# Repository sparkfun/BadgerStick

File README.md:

Interactive Badges
==================

 [*SparkFun BadgerHack *](https://learn.sparkfun.com/tutorials/badgerhack)
 
 These badges were designed as a soldering demo for the SparkFun booths at Maker Faire. 
 They were designed to teach the basics of PTH soldering, as well as to provide users with an Arduino platform they could take home and hack.
 
Please view the [BadgerHack tutorial](https://learn.sparkfun.com/tutorials/badgerhack) for more information on updating the firmware, and further experiments with your badge. 
 
 Repository Contents
-------------------

* **/badgerstick/avr** - Board definition files for Arduino.
* **/Documentation** - SoftwareSerial Baud Rate table
* **/Firmware** - Default firmware that ships on the BadgerStick
* **/Hardware** - All Eagle design files (.brd, .sch)
* **/Production** - Test bed files and production panel files

Documentation
--------------
* **[Library](https://github.com/sparkfun/SparkFun_LED_Array_8x7_Arduino_Library)** - Arduino library for the BadgerStick.
* **[Hookup Guide](https://learn.sparkfun.com/tutorials/badgerhack)** - Basic hookup guide for the BadgerStick. 
* **[SparkFun Fritzing repo](https://github.com/sparkfun/Fritzing_Parts)** - Fritzing diagrams for SparkFun products.
* **[SparkFun 3D Model repo](https://github.com/sparkfun/3D_Models)** - 3D models of SparkFun products. 
* **[SparkFun Graphical Datasheets](https://github.com/sparkfun/Graphical_Datasheets)** -Graphical Datasheets for various SparkFun products.

License Information
-------------------

This product is _**open source**_! 

Please review the LICENSE.md file for license information. 

If you have any questions or concerns on licensing, please contact techsupport@sparkfun.com.

Distributed as-is; no warranty is given.

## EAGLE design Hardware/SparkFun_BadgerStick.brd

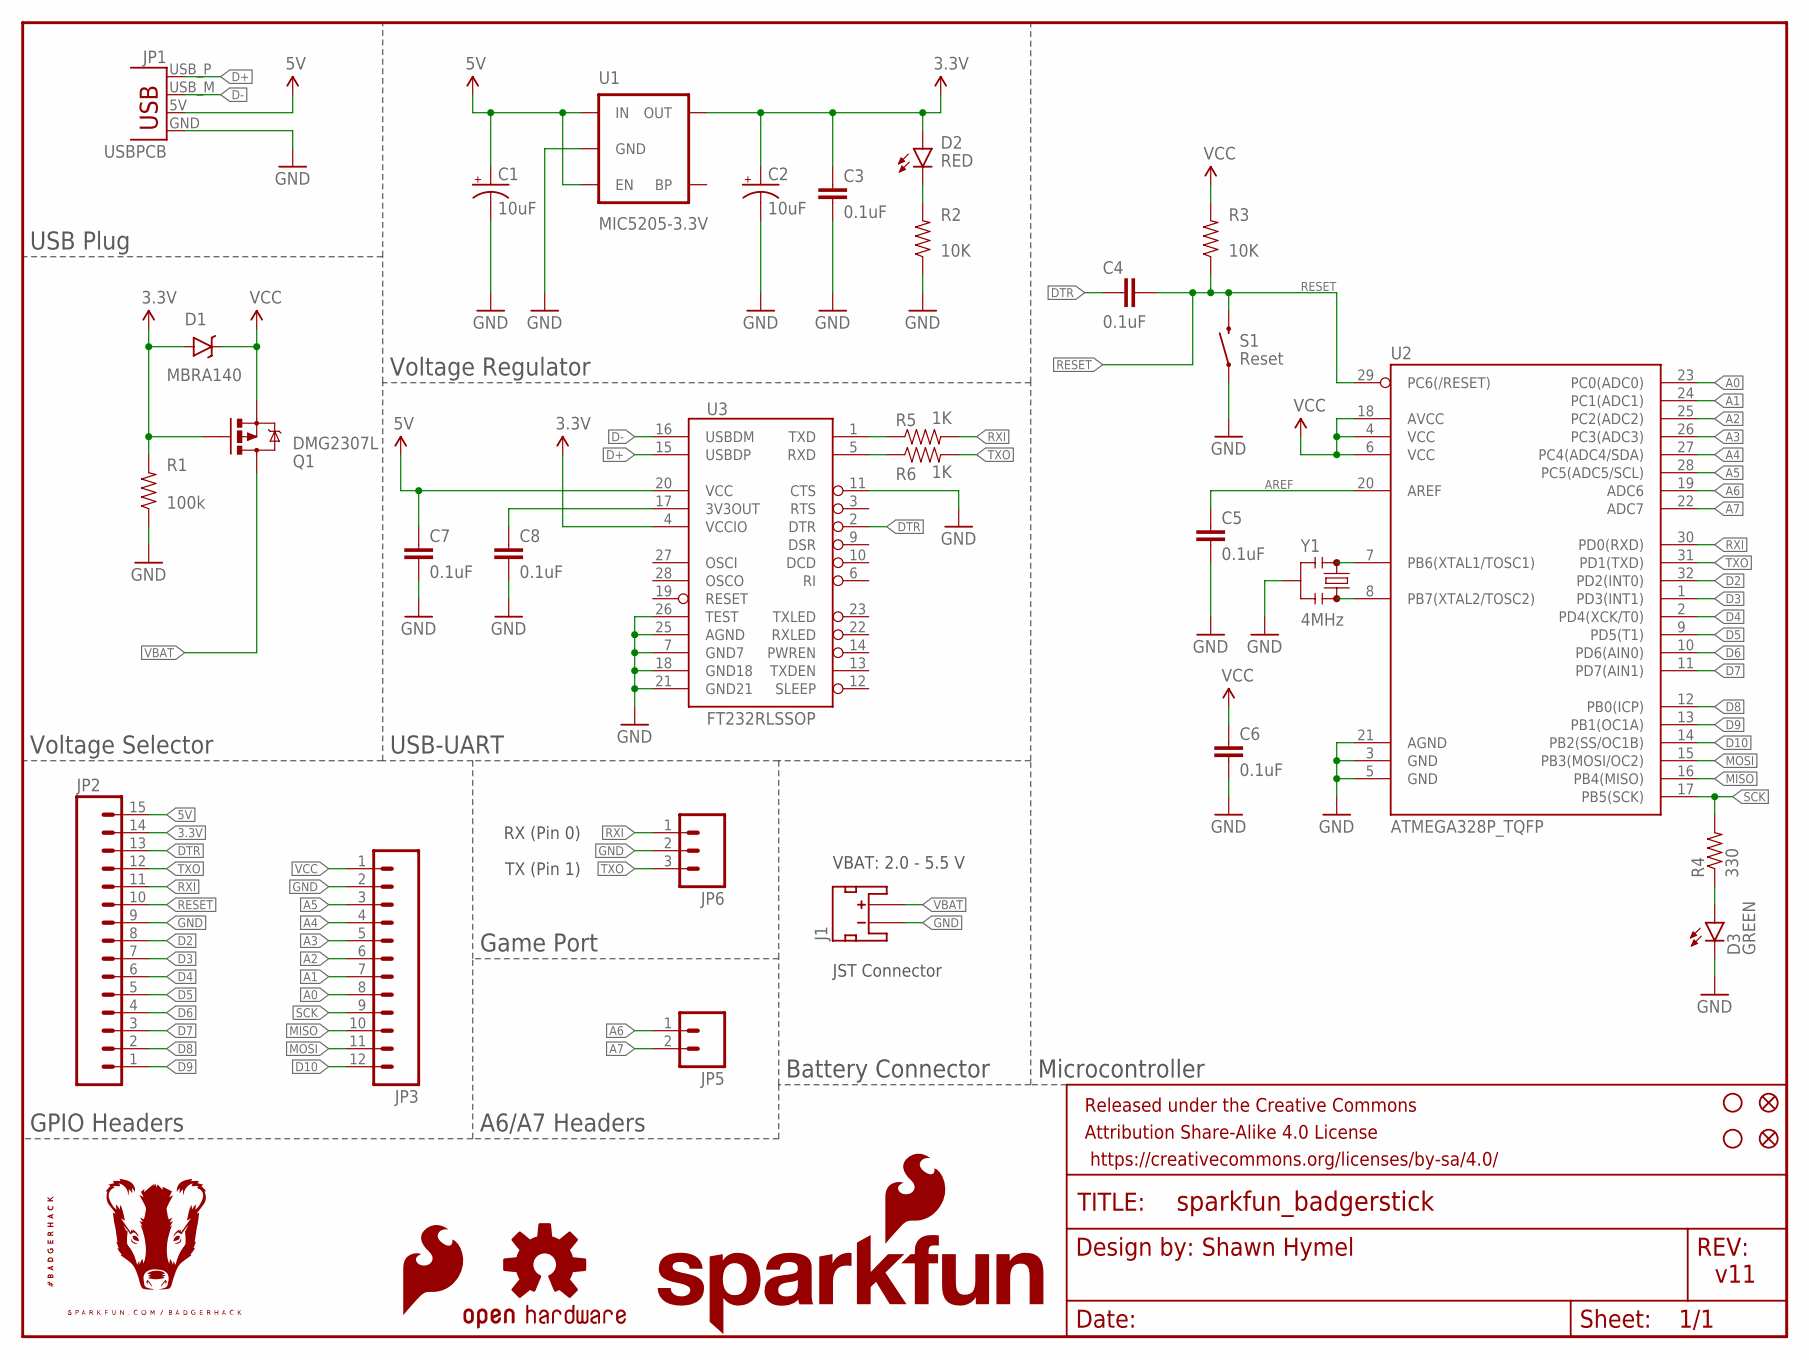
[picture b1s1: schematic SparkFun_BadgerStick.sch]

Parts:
C1, C2: 10uF; EIA3216
C3, C4, C5, C6, C7, C8: 0.1uF; 0603-CAP
D1: MBRA140; SMA-DIODE
D2: RED; LED-0603
D3: GREEN; LED-0603
FID1, FID2: FIDUCIAL1X2; FIDUCIAL-1X2
FRAME1: FRAME-LETTER; CREATIVE_COMMONS
J1: JST_2MM_MALE; JST-2-SMD
JP1: USBPCB; USB-A-PCB
JP2: M15LOCK_NO_SILK; 1X15_LOCK_NO_SILK
JP3: M12LOCK_NO_SILK; 1X12_LOCK_NO_SILK
JP5: M021X02_NO_SILK; 1X02_NO_SILK
JP6: M03LOCK Female; 1X03_LOCK_NO_SILK
LOGO1: SFE_LOGO_FLAME.1_INCH; SFE_LOGO_FLAME_.1
LOGO2: OSHW-LOGOS; OSHW-LOGO-S
Q1: DMG2307L; SOT23-3
R1: 100k; 0603-RES
R2, R3: 10K; 0603-RES
R4: 330; 0603-RES
R5, R6: 1K; 0603-RES
S1: SWITCH-MOMENTARY-2SMD-REDUNDANT; TACTILE-SWITCH-SMD
STANDOFF1, STANDOFF2: STAND-OFF
U1: MIC5205-3.3V; SOT23-5
U2: ATMEGA328P_TQFP; TQFP32-08
U3: FT232RLSSOP; SSOP28DB
U$1: SFE_LOGO_NAME_FLAME.1_INCH; SFE_LOGO_NAME_FLAME_.1
U$2: BADGERHACK_LOGODUMMY; DUMMY
Y1: 4MHz; RESONATOR-SMD_MED

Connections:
3.3V: C2.A (+), C3.1, D1.A, D2.A, JP2.14, Q1.1 (G), R1.2, U1.5 (OUT), U3.4 (VCCIO)
5V: C1.A (+), C7.1, JP1.5V (VBUS), JP2.15, U1.1 (IN), U1.3 (EN), U3.20 (VCC)
A0: JP3.8, U2.23 (PC0(ADC0))
A1: JP3.7, U2.24 (PC1(ADC1))
A2: JP3.6, U2.25 (PC2(ADC2))
A3: JP3.5, U2.26 (PC3(ADC3))
A4: JP3.4, U2.27 (PC4(ADC4/SDA))
A5: JP3.3, U2.28 (PC5(ADC5/SCL))
A6: JP5.1, U2.19 (ADC6)
A7: JP5.2, U2.22 (ADC7)
AREF: C5.1, U2.20 (AREF)
D2: JP2.8, U2.32 (PD2(INT0))
D3: JP2.7, U2.1 (PD3(INT1))
D4: JP2.6, U2.2 (PD4(XCK/T0))
D5: JP2.5, U2.9 (PD5(T1))
D6: JP2.4, U2.10 (PD6(AIN0))
D7: JP2.3, U2.11 (PD7(AIN1))
D8: JP2.2, U2.12 (PB0(ICP))
D9: JP2.1, U2.13 (PB1(OC1A))
D10: JP3.12, U2.14 (PB2(SS/OC1B))
D+: JP1.USB_P (D+), U3.15 (USBDP)
D-: JP1.USB_M (D-), U3.16 (USBDM)
DTR: C4.1, JP2.13, U3.2 (DTR)
GND: C1.C (-), C2.C (-), C3.2, C5.2, C6.2, C7.2, C8.2, D3.C, J1.1 (-), JP1.GND, JP2.9, JP3.2, JP6.2, R1.1, R2.1, S1.1, S1.2 (1), U1.2 (GND), U2.3 (GND), U2.5 (GND), U2.21 (AGND), U3.7 (GND7), U3.11 (CTS), U3.18 (GND18), U3.21 (GND21), U3.25 (AGND), U3.26 (TEST), Y1.2
MISO: JP3.10, U2.16 (PB4(MISO))
MOSI: JP3.11, U2.15 (PB3(MOSI/OC2))
unnamed: D3.A, R4.1
unnamed: C8.1, U3.17 (3V3OUT)
unnamed: R5.1, U3.1 (TXD)
unnamed: D2.C, R2.2
unnamed: U2.7 (PB6(XTAL1/TOSC1)), Y1.1
unnamed: U2.8 (PB7(XTAL2/TOSC2)), Y1.3
unnamed: R6.1, U3.5 (RXD)
RESET: C4.2, JP2.10, R3.1, S1.3 (2), S1.4 (2), U2.29 (PC6(/RESET))
RXI: JP2.11, JP6.1, R5.2, U2.30 (PD0(RXD))
SCK: JP3.9, R4.2, U2.17 (PB5(SCK))
TXO: JP2.12, JP6.3, R6.2, U2.31 (PD1(TXD))
VBAT: J1.2 (+), Q1.3 (D)
VCC: C6.1, D1.C, JP3.1, Q1.2 (S), R3.2, U2.4 (VCC), U2.6 (VCC), U2.18 (AVCC)

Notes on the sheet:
RX (Pin 0)
TX (Pin 1)
USB Plug
Voltage Selector
GPIO Headers
A6/A7 Headers
Game Port
USB-UART
Voltage Regulator
Microcontroller
Battery Connector
VBAT: 2.0 - 5.5 V
JST Connector

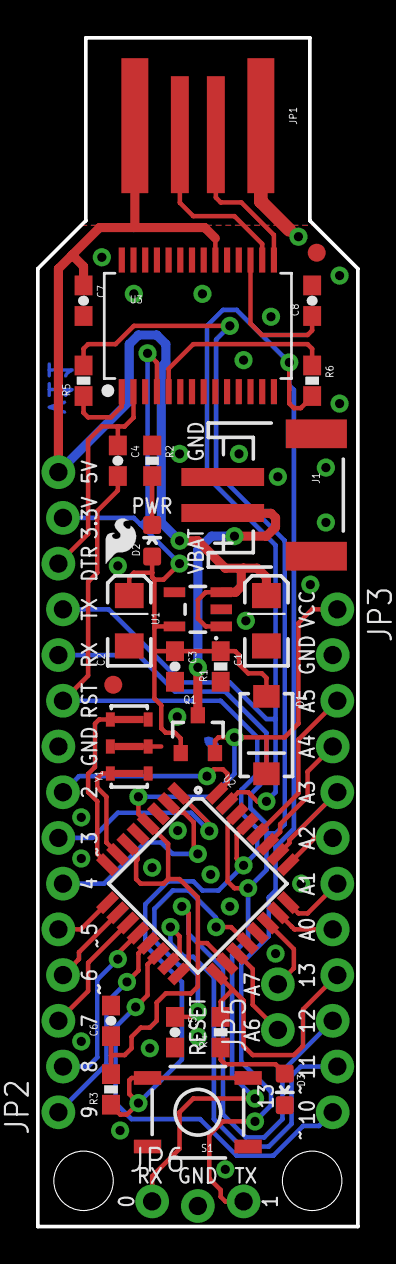
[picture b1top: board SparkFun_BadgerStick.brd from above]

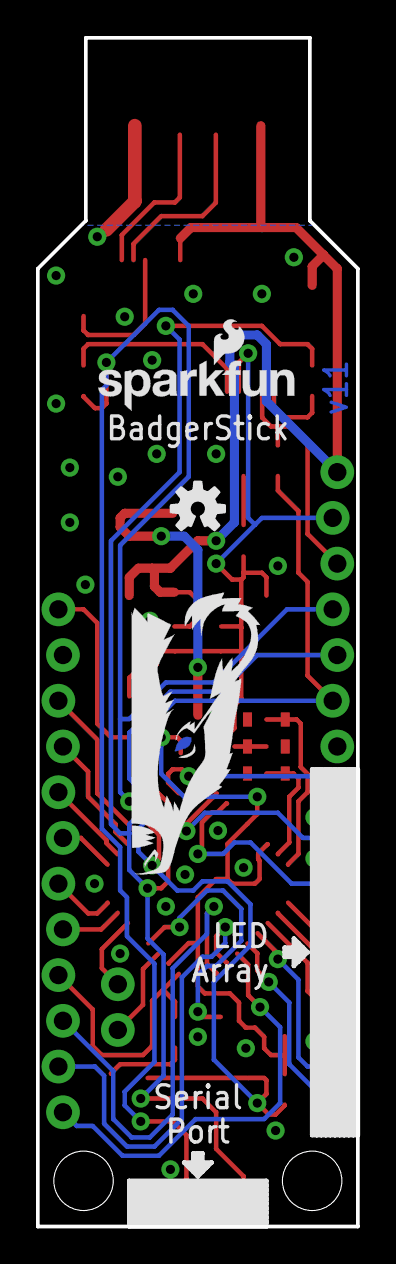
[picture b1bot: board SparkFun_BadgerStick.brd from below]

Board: 2 copper layers, 17.8 x 66.0 mm, 39 parts (3 on the bottom side), 39 nets.

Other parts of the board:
U$3: HALF_BADGER

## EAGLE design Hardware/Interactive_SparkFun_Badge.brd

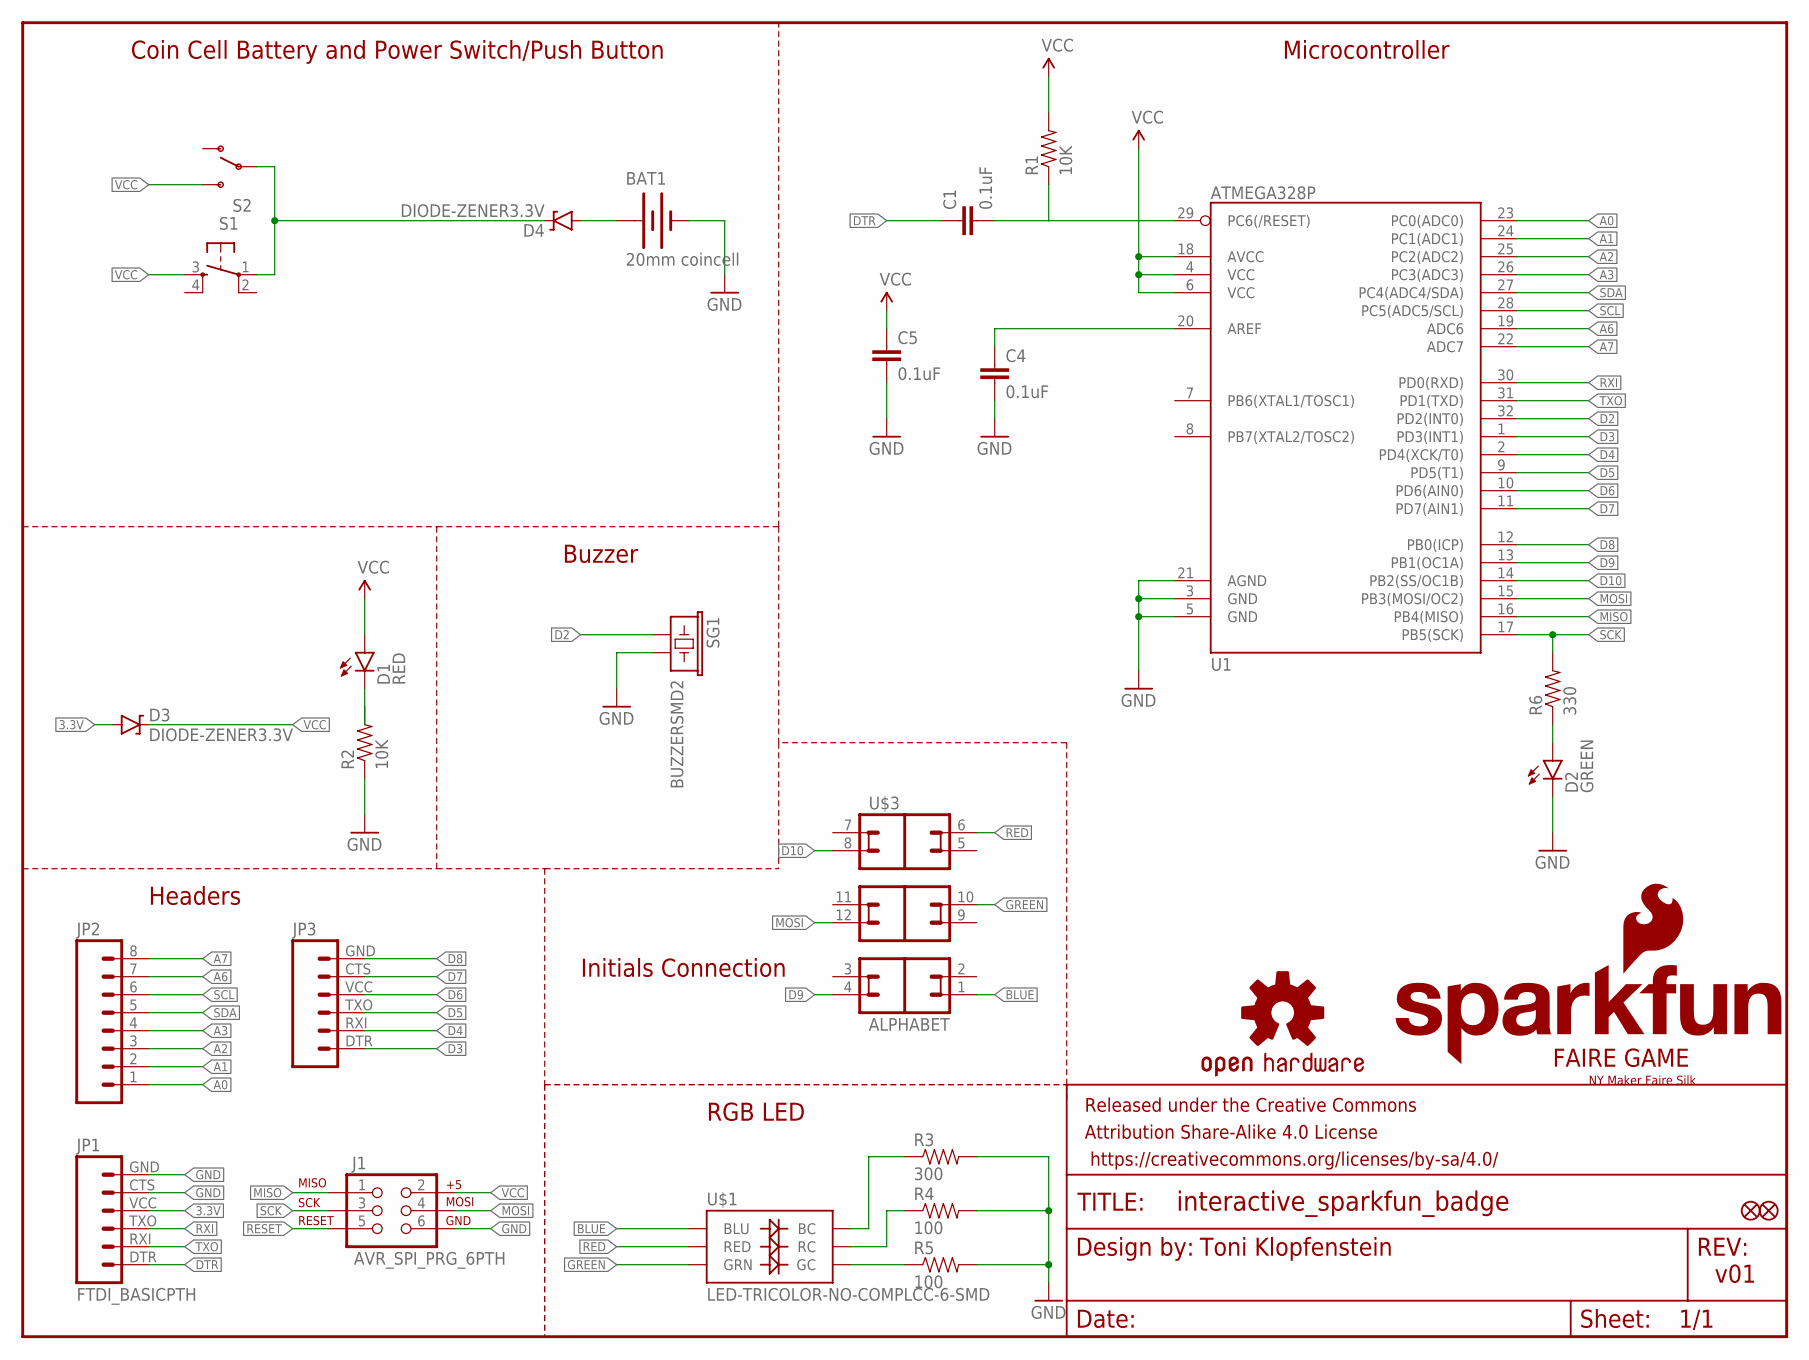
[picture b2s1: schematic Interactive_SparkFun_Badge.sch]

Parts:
BAT1: 20mm coincell; BATTCON_20MM_4LEGS
C1, C4, C5: 0.1uF; 0603-CAP
D1: RED; LED-0603
D2: GREEN; LED-0603
D3, D4: DIODE-ZENER3.3V; SOD-323
FID1, FID2: FIDUCIAL1X2; FIDUCIAL-1X2
FRAME1: FRAME-LETTER; CREATIVE_COMMONS
J1: AVR_SPI_PRG_6PTH; 2X3
JP1: FTDI_BASICPTH; FTDI_BASIC
JP2: M081X08; 1X08
JP3: M06SIP; 1X06
LOGO1: OSHW-LOGOM; OSHW-LOGO-M
R1, R2: 10K; 0603-RES
R3: 300; 0603-RES
R4, R5: 100; 0603-RES
R6: 330; 0603-RES
S1: TAC_SWITCHSMD; TACTILE-SWITCH-SMD
S2: SWITCH-SPDTSMD; AYZ0202
SG1: BUZZERSMD2; BUZZER-CCV
U1: ATMEGA328P; TQFP32-08
U$1: LED-TRICOLOR-NO-COMPLCC-6-SMD; PLCC-6-LED
U$2: NY_FAIRE_BACK; NY_BACK
U$3: ALPHABET; INITIALS
U$4: FAIRE_GAME_SILK

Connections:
3.3V: D3.A, JP1.VCC (4)
A0: JP2.1, U1.23 (PC0(ADC0))
A1: JP2.2, U1.24 (PC1(ADC1))
A2: JP2.3, U1.25 (PC2(ADC2))
A3: JP2.4, U1.26 (PC3(ADC3))
A6: JP2.7, U1.19 (ADC6)
A7: JP2.8, U1.22 (ADC7)
BLUE: U$1.AB (BLU), U$3.1
D2: SG1.+ (1), U1.32 (PD2(INT0))
D3: JP3.DTR (1), U1.1 (PD3(INT1))
D4: JP3.RXI (2), U1.2 (PD4(XCK/T0))
D5: JP3.TXO (3), U1.9 (PD5(T1))
D6: JP3.VCC (4), U1.10 (PD6(AIN0))
D7: JP3.CTS (5), U1.11 (PD7(AIN1))
D8: JP3.GND (6), U1.12 (PB0(ICP))
D9: U1.13 (PB1(OC1A)), U$3.4
D10: U1.14 (PB2(SS/OC1B)), U$3.8
DTR: C1.1, JP1.DTR (1)
GND: BAT1.2 (-), C4.2, C5.2, D2.C, J1.6, JP1.CTS (5), JP1.GND (6), R2.1, R3.2, R4.2, R5.2, SG1.- (2), U1.3 (GND), U1.5 (GND), U1.21 (AGND)
GREEN: U$1.AG (GRN), U$3.10
MISO: J1.1, U1.16 (PB4(MISO))
MOSI: J1.4, U1.15 (PB3(MOSI/OC2)), U$3.12
unnamed: D4.C, S1.1, S2.2
unnamed: R3.1, U$1.CB (BC)
unnamed: D1.C, R2.2
unnamed: R4.1, U$1.CR (RC)
unnamed: R5.1, U$1.CG (GC)
unnamed: C4.1, U1.20 (AREF)
unnamed: D2.A, R6.1
unnamed: BAT1.1 (+), D4.A
RED: U$1.AR (RED), U$3.6
RESET: C1.2, J1.5, R1.1, U1.29 (PC6(/RESET))
RXI: JP1.TXO (3), U1.30 (PD0(RXD))
SCK: J1.3, R6.2, U1.17 (PB5(SCK))
SCL: JP2.6, U1.28 (PC5(ADC5/SCL))
SDA: JP2.5, U1.27 (PC4(ADC4/SDA))
TXO: JP1.RXI (2), U1.31 (PD1(TXD))
VCC: C5.1, D1.A, D3.C, J1.2, R1.2, S1.3, S2.3 (S), U1.4 (VCC), U1.6 (VCC), U1.18 (AVCC)

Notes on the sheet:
v01
Toni Klopfenstein
RGB LED
Coin Cell Battery and Power Switch/Push Button
Buzzer
Microcontroller
Headers
Initials Connection

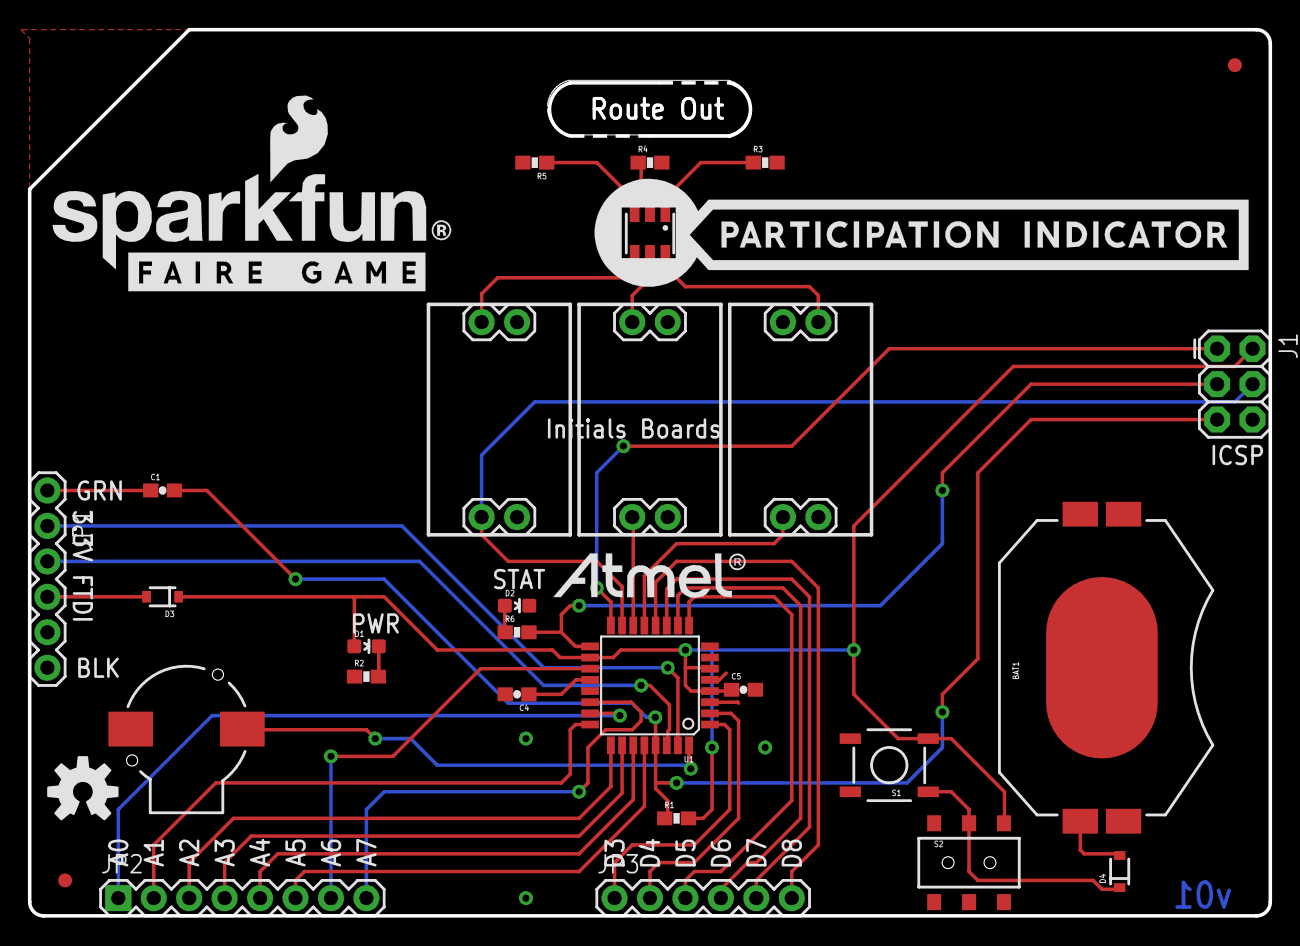
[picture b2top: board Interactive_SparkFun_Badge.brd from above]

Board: 2 copper layers, 88.9 x 63.5 mm, 30 parts (0 on the bottom side), 38 nets.

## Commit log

2014-06-20 Adding initial board design files
2014-06-23 moving oscillator
2014-06-23 Updating line widths
2014-07-01 New board design
2014-07-02 Updating with engineering review changes
2014-08-05 Updating to round corners, zener diodes, larger letter boards
2014-08-06 Updating to new power circuit, and adding front silk
2014-08-06 Adding NY MF silk
2014-08-21 Fixing line widths in schematic
2014-09-04 Badge Firmware
    Uploaded firmware to be slammed onto the final production badges!
2014-09-24 Update README.md
    Adding in general product description, repo info, and link to tutorial.
2014-12-10 Removed old badge hardware files.
2014-12-12 Started schematic. Voltage selection circuit added.
2014-12-12 Added LDO to power section in sch
2014-12-13 Finished initial sch. Mock-up layout
2014-12-14 Added PTH UART header on bottom. Added outline of wing on tDocu layer.
2014-12-15 Added Misc folder to .gitignore
2014-12-16 Initial layout complete
2014-12-16 Added mounting holes in brd. Still need to fix 2 air wires.
2014-12-16 Finished layout. Need to move some components to accomodate silk numbers.
2014-12-16 Moved pins. Added silk.
2014-12-16 Added bottom silk. Added A6, A7 silk.
2014-12-16 Colored in silk for required headers.
2014-12-16 Updated frame with name
2014-12-17 Added 4MHz resonator.
2014-12-18 Fixed route out of D2. Added silk for TX and RX on Game Port. Added dimensions.
2014-12-18 Changed 'Badger Stick' to 'BadgerStick' in silk.
2014-12-19 Added badger logo.
2014-12-19 Added half-badger logo.
2014-12-22 Added badge dimensions on custom layer.
2014-12-22 Fixed changes from QC checklist. Made all 'Y' juntions into 'T' junctions. Added PWR and LED silk. Moved dimensions to layer 47. Removed 'values' from headers in sch and brd.
2015-01-22 Updated to v10
2015-01-22 Removed bridge between pads on Cypress. Removed extraneous measurements outside of board.
2015-01-23 created panel v10
2015-01-23 Added board definition and bootloader files for the BadgerStick.
2015-02-13 Created initial badge firmware
2015-02-13 Added stations and alpha station code
2015-02-13 Adding Production Test Code
    Including preliminary production Test Code that will be integrated into
    final badge firmware
2015-02-14 Added production test code, animations, 2-byte station values, and coupon code storage.
2015-02-14 Added win condition checking and animation. Removed production test code and Alpha Station prototype code.
2015-02-16 Added Make It Rain animation. Removed SparkFun scrolling text. Removed DEBUG flag.
2015-02-16 Added Badge ID checking to win conditions. Changed order of animations. Added Station ID constant to station code.
2015-02-18 Cleaning up test code
    Making test code more efficient. Removing test mode check function and
    making eeprom read in setup just run test code directly if test pass
    value not set.
2015-02-19 Lessing delay after successful test
    Delay was 5 seconds. Shortening it to 2 seconds per production feedback.
2015-02-19 Updating Station Firmware
    BadgerSX15_Stations.ino is now the firmware being shipped on ARM's
    station (non-alpha station 0x01)
2015-04-13 More re-routing for v11 of the BadgerStick.
2015-04-13 Replaced battery pins with JST, added inline resistors to FTDI, and changed Game Port pins to hardware UART. Began routing new lines. Not finished. Removed SVG files of layout (outdated).
2015-04-13 Finished new layout with JST, inline resistors (UART), and 0/1 pin game port.
2015-04-14 Adjusted vias to allow for 2 connections to GND from 328p. Moved silk slightly to avoid vias (as possible).
2015-04-20 Changed LED silk to '13'. Added notes to sch about voltage range and JST connector. Moved wire in sch for VCC on 328p to avoid confusion with the RESET line.
2015-04-28 Corrected eagle file names
    Corrected to "BadgerStick"
2015-04-28 Changed dimension thickness, added silk to reset button, and removed pour bridge under FTDI.
2015-05-28 Moved board definition files to separate badgerstick directory.
2015-06-01 Changed baud to 250000. Moved bootloader files out of separate avr directory.
2015-08-19 Created NMMF15_Badges sketch and added SoftwareSerial library.
2015-08-19 Action cycle added with growing flame animation and initial text
2015-08-21 Added Conway's Game of Live to the NMMF code
2015-08-25 Remvoed flickering in frames. Adjusted number of max actions to 30
2015-08-25 Changed all array stuffs to EEPROM
2015-08-26 Initial comms working. Stick fails to get full message sometimes.
2015-08-27 It works! Mwahahaha! Transferring works. Still some flicker between actions.
2015-08-27 Fixed flickering
2015-09-04 Flipped flame image
2015-09-10 Updated boards.txt with variant variable
2016-01-18 Updated boards.txt to work with arduino 1.6.6 and 1.6.7
2016-02-16 Switched Cypress USB-Serial bridge to FT232RL
2016-03-02 Fixing directory names, adding license file, updating README with tutorial links
2016-03-02 Adding changed directories
2016-03-02 Fixing badge image url
2016-03-09 Adding the latest badger station firmware.
2016-03-12 Separated station sxsw2016 code into A and B stations. Cleaned up keypad code

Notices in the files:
parts and their libraries:
SparkFun-Aesthetics: Licensing: Creative Commons ShareAlike 4.0 International - https://creativecommons.org/licenses/by-sa/4.0
SparkFun-Aesthetics: Released under the Creative Commons Attribution Share-Alike 4.0 License
SparkFun-Aesthetics: https://creativecommons.org/licenses/by-sa/4.0
